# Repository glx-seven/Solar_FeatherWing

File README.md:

# Solar_FeatherWing
##  Description
Run your projects with free sun-power :).

The ST SPV1040 takes care of the MPPT of your solar-panel.
An integrated TI INA219 power monitor IC (at I2C address 0x48) lets you observe your battery voltage and the charge/discharge rate.

The maximum voltage of the solar-cell is 5.5V. 
Never connect batteries on your feather board (or anywhere else) and this wing at the same time.

## BOM
| Part | Value | Package | Description |
| --- | --- | --- | --- |
| C1 | 22uF | C0603K | capacitor |
| C2 | 22uF | C0603K   | capacitor |
| C3 | 1nF | C0603K | capacitor |
| C4 | 1nF | C0603K | capacitor |
| C5 | 1uF | C0603K | capacitor |
| C6 | 22uF | C0603K | capacitor |
| C7 | 22uF | C0603K | capacitor |
| C8 | 22uF | C0603K | capacitor |
| C10 | 100nF | C0603K | capacitor |
| D1 | NSR0530HT1G | SOD323 | diode |
| D2 | SMBJ5339B-TP | SMB | z-diode for protection |
| IC1 | SPV1040T | TSSOP8 | Solar-charge IC |
| IC2 | INA219AIDCNR | SOT65P280X145-8N | power monitor |
| J1 | 1X2-3.5MM | 1X2-3.5MM | terminal header |
| L1 | 10uH | DR74 | inductor | Shielded Iinductor |
| MS1 | FEATHERWING | FEATHERWING | adafruit featherwing layout |
| R1 | 1k | R0603 | resistor |
| R2 | 50m | R0603 | resistor; current-limit of the charger |
| R3 | 1k | R0603 | resistor |
| R4 | 1k | R0603 | resistor |
| R5 | 1.2M | R0603 | resistor |
| R6 | 390k | R0603 | resistor |
| R7 | 100m | R1206 | resistor; shunt resistor for current-measurement |
| R8 | 4.7k | R0603 | resistor; i2c pullup |
| R9 | 4.7k | R0603 | resistor; i2c pullup |

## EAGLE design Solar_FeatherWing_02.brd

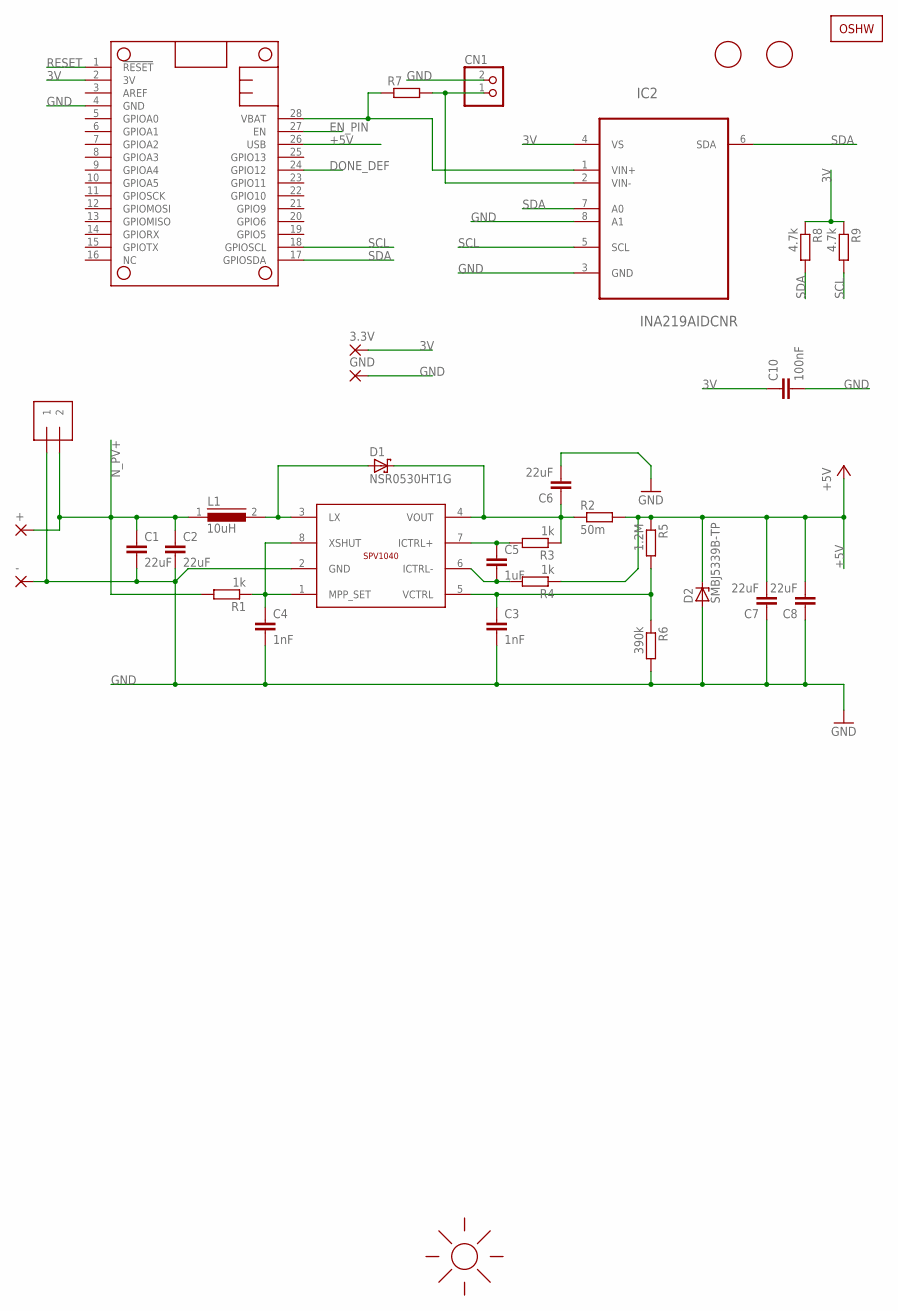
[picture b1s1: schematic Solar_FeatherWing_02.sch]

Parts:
3.3V: 1,6/0,9
+: 1,6/0,9
-: 1,6/0,9
C1, C2, C6, C7, C8: 22uF; C0603K
C3, C4: 1nF; C0603K
C5: 1uF; C0603K
C10: 100nF; C0603K
CN1: JST_2PIN-SMT-RA; JST-PH-2-SMT-RA
D1: NSR0530HT1G; SOD323_ST
D2: SMBJ5339B-TP; SMB
GND: 1,6/0,9
IC1: SPV1040T; TSSOP8
IC2: INA219AIDCNR; SOT65P280X145-8N
J1: 1X2-3.5MM
L1: 10uH; DR74
LOGO1: OSHW_LOGOX0100; OSHW_6X100
MS1: FEATHERWING
R1, R3, R4: 1k; R0603
R2: 50m; R0603
R5: 1.2M; R0603
R6: 390k; R0603
R7: R-EU_R1206; R1206
R8, R9: 4.7k; R0603
U$1: SUNLOGO; SUN
U$2, U$3: FIDUCIAL; FIDUCIAL_1MM

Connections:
3V: 3.3V.1, C10.1, IC2.4 (VS), MS1.2 (3V), R8.1, R9.1
+5V: C7.2, C8.2, D2.C, MS1.26 (USB), R2.2, R4.1, R5.1
DONE_DEF: MS1.24 (GPIO12)
EN_PIN: MS1.27 (EN)
GND: -.1, C1.2, C2.2, C3.2, C4.2, C6.2, C7.1, C8.1, C10.2, CN1.2 (1), D2.A, GND.1, IC1.2 (GND), IC2.3 (GND), IC2.8 (A1), J1.1, MS1.4 (GND), R6.2
LX: D1.A, IC1.3 (LX), L1.2
unnamed: C4.1, IC1.1 (MPP_SET), IC1.8 (XSHUT), R1.1
unnamed: C5.1, IC1.7 (ICTRL+), R3.2
unnamed: C5.2, IC1.6 (ICTRL-), R4.2
unnamed: C6.1, D1.C, IC1.4 (VOUT), R2.1, R3.1
unnamed: CN1.1 (2), IC2.2 (VIN-), R7.2
N_PV+: +.1, C1.1, C2.1, J1.2, L1.1, R1.2
N_VCTRL: C3.1, IC1.5 (VCTRL), R5.2, R6.1
RESET: MS1.1 (!RESET)
SCL: IC2.5 (SCL), MS1.18 (GPIOSCL), R9.2
SDA: IC2.6 (SDA), IC2.7 (A0), MS1.17 (GPIOSDA), R8.2
VBAT: IC2.1 (VIN+), MS1.28 (VBAT), R7.1

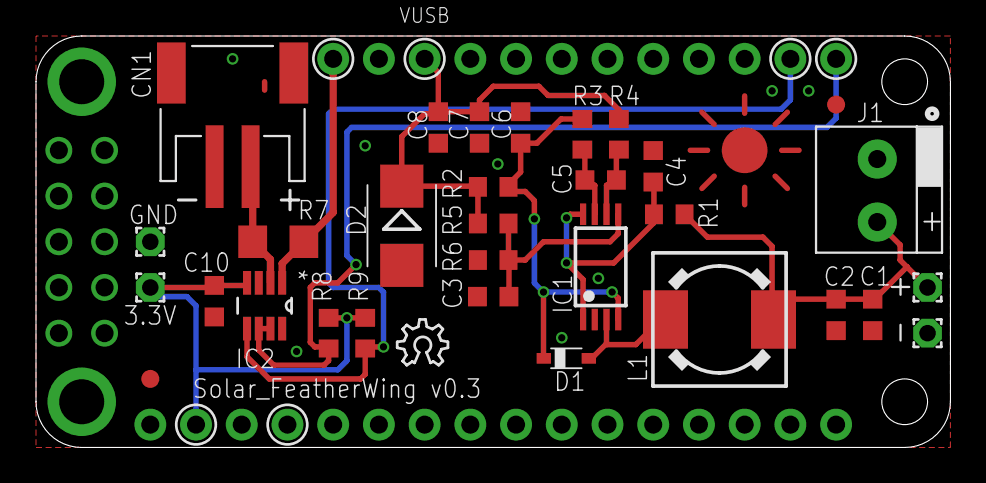
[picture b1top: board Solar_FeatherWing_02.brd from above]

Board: 2 copper layers, 50.8 x 22.9 mm, 34 parts (0 on the bottom side), 14 nets.

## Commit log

2019-07-25 Initial release
2019-11-04 Changed features
    Removed the timer-ic and added a INA219 to monitor power.
2019-11-05 Monitor battery current and voltage
2019-11-05 Updated documentation
